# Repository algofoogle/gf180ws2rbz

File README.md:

# gf180ws2rbz: Raybox-zero supporting materials

For now, this is just a test PCB for various parts that could be used to support a raybox-zero devkit.

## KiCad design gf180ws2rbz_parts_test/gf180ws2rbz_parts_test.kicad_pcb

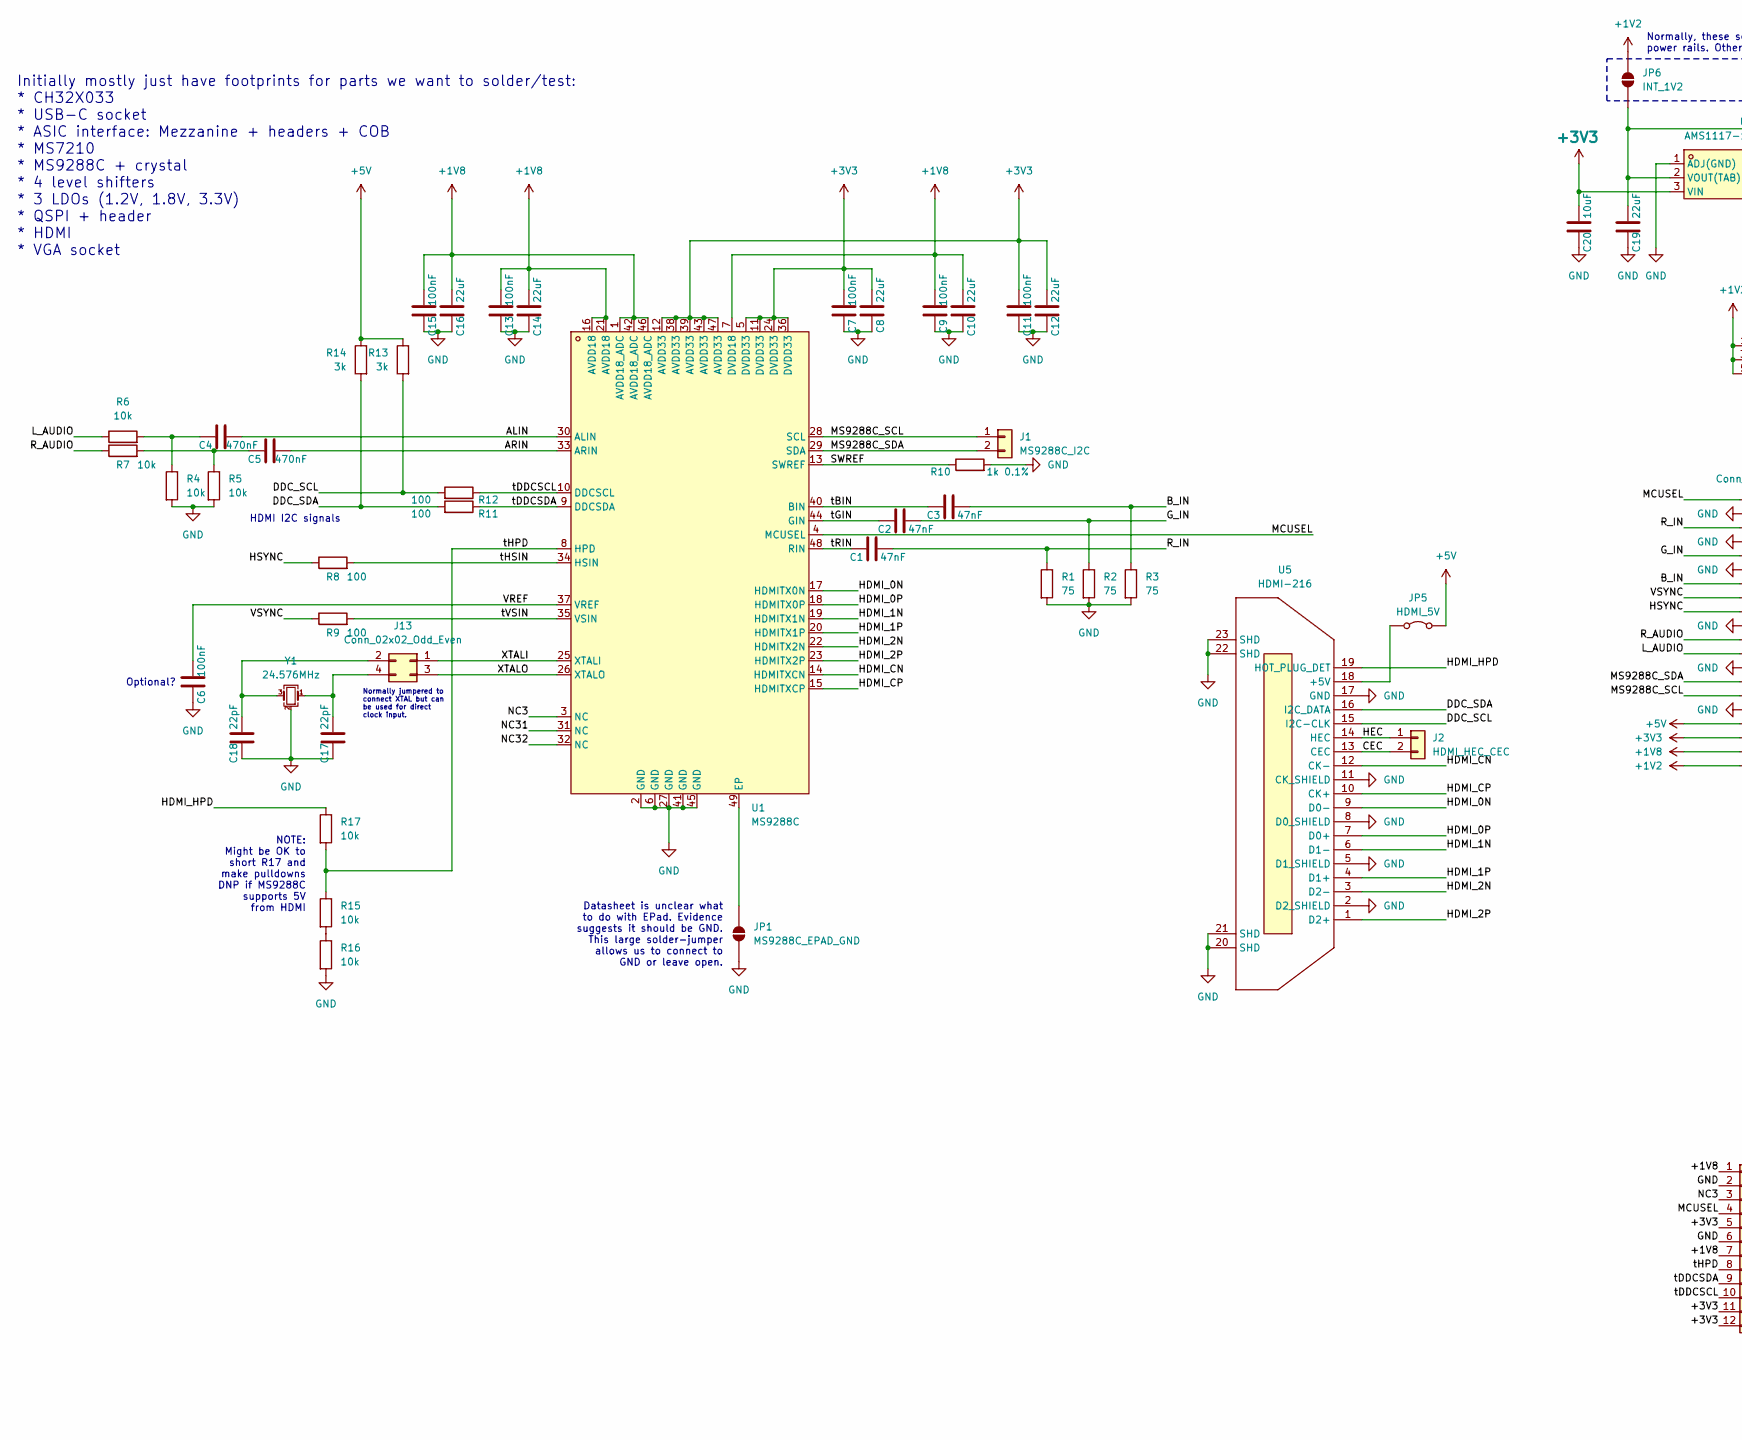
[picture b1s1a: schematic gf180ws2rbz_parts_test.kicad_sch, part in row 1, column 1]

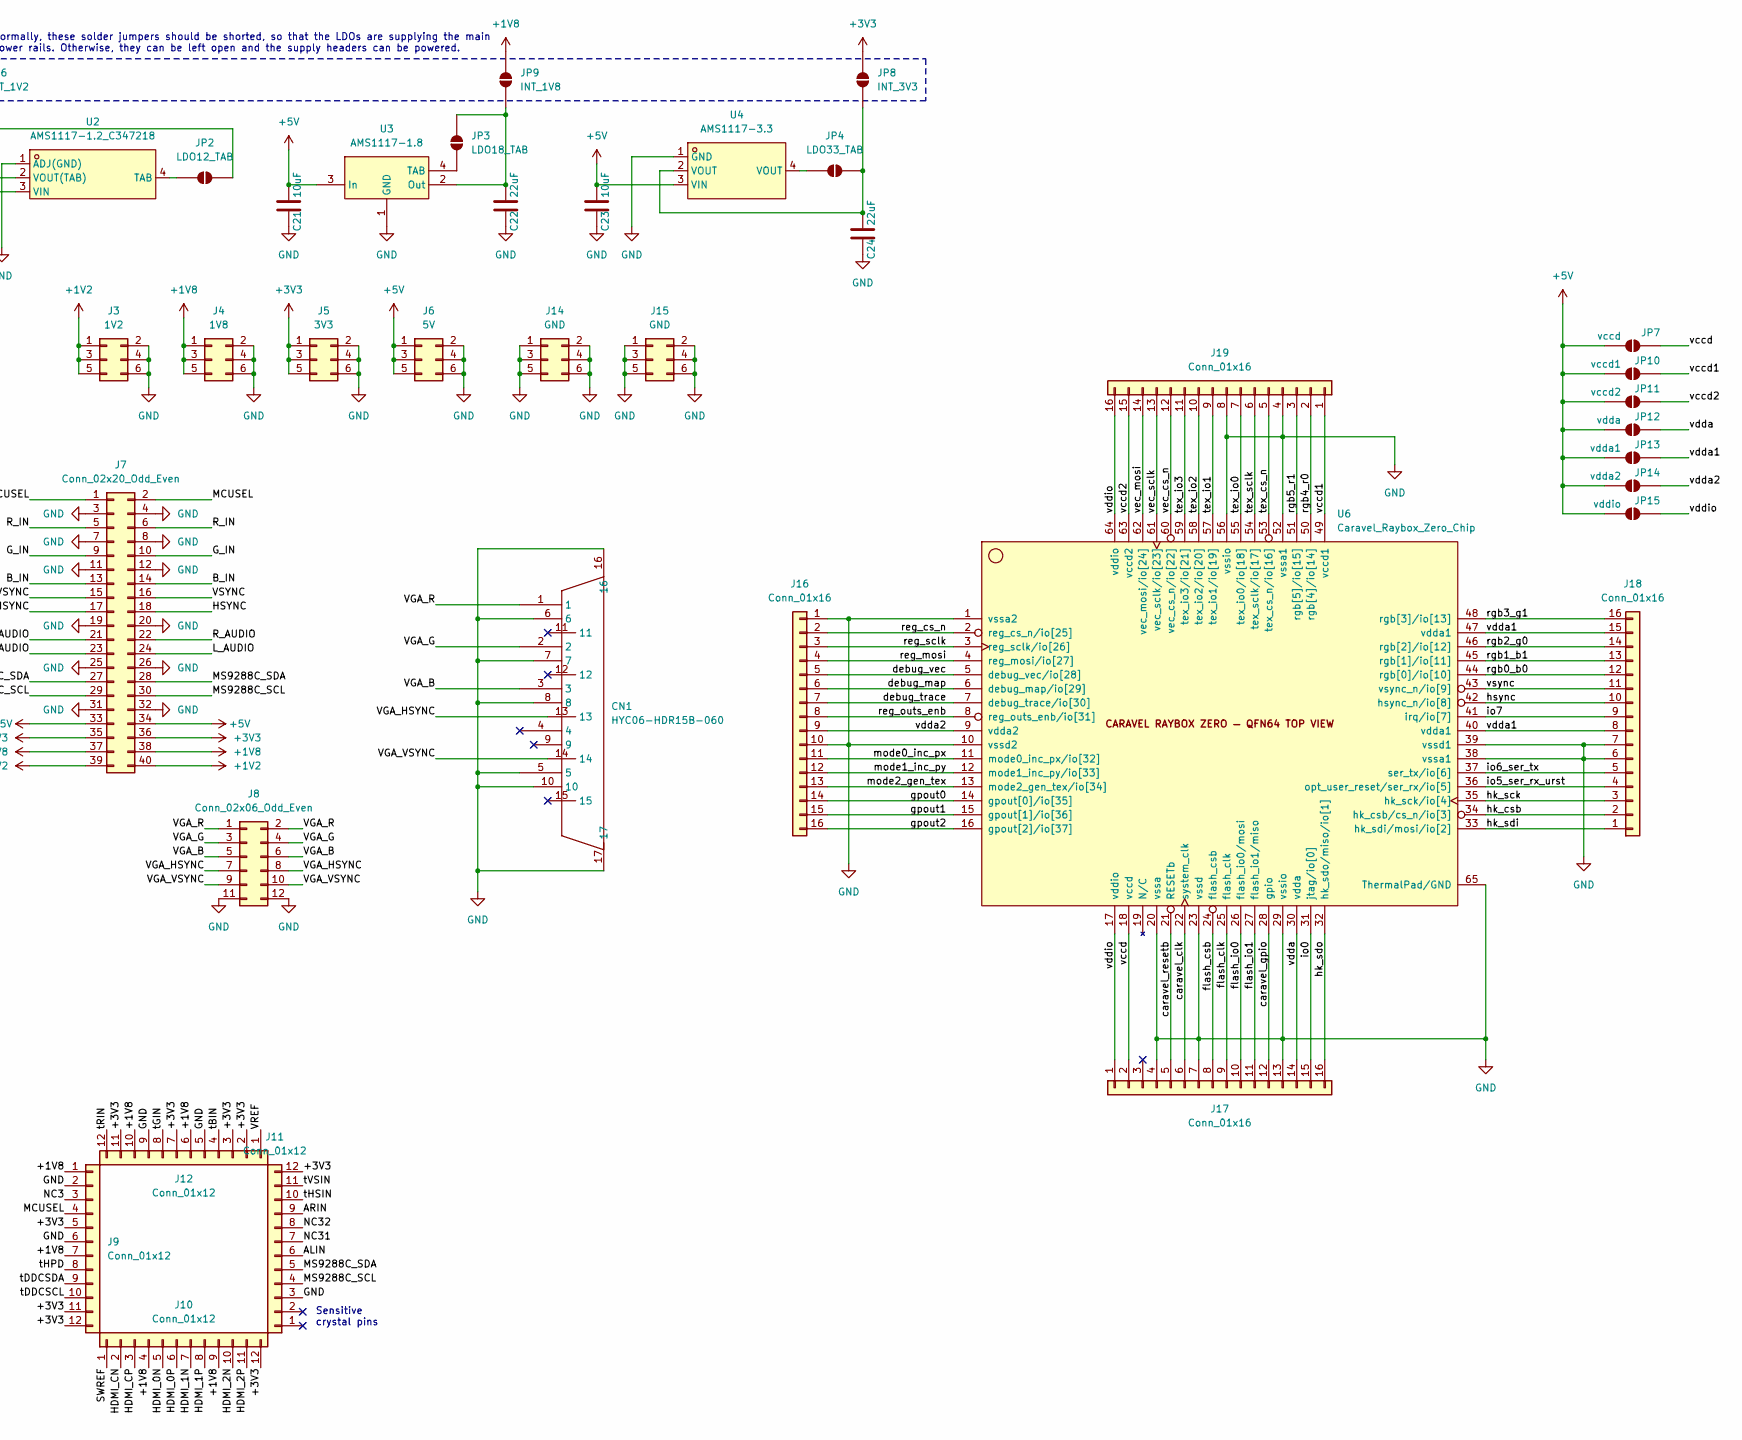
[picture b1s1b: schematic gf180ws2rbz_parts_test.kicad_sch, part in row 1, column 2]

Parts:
C1, C2, C3: 47nF; C_0603_1608Metric_Pad1.08x0.95mm_HandSolder
C4, C5: 470nF; C_0603_1608Metric_Pad1.08x0.95mm_HandSolder
C6, C7, C9, C11, C13, C15: 100nF; C_0603_1608Metric_Pad1.08x0.95mm_HandSolder
C8, C10, C12, C14, C16, C19, C22, C24: 22uF; C_0603_1608Metric_Pad1.08x0.95mm_HandSolder
C17, C18: 22pF; C_0603_1608Metric_Pad1.08x0.95mm_HandSolder
C20, C21, C23: 10uF; C_0603_1608Metric_Pad1.08x0.95mm_HandSolder
CN1: HYC06-HDR15B-060; DSUB-TH_HYC06-HDR15B-060; MPN HYC06-HDR15B-060; LCSC Part C711364
J1: MS9288C_I2C; PinHeader_1x02_P2.54mm_Vertical
J2: HDMI_HEC_CEC; PinHeader_1x02_P2.54mm_Vertical
J3: 1V2; PinHeader_2x03_P2.54mm_Vertical
J4: 1V8; PinHeader_2x03_P2.54mm_Vertical
J5: 3V3; PinHeader_2x03_P2.54mm_Vertical
J6: 5V; PinHeader_2x03_P2.54mm_Vertical
J7: Conn_02x20_Odd_Even; PinHeader_2x20_P2.54mm_Vertical
J8: Conn_02x06_Odd_Even; PinHeader_2x06_P2.54mm_Vertical
J9, J10, J11, J12: Conn_01x12; AntonPTHTestPointStagger12way
J13: Conn_02x02_Odd_Even; Anton-PinSocket_2x02_P2.54mm_Vertical-SolderJumper
J14, J15: GND; PinHeader_2x03_P2.54mm_Vertical
J16, J17, J18, J19: Conn_01x16; Anton_Pads_01x16_1.27mm_Compact_SMD
JP1: MS9288C_EPAD_GND; SolderJumper-2_P1.3mm_Open_RoundedPad1.0x1.5mm
JP2: LDO12_TAB; SolderJumper-2_P1.3mm_Open_RoundedPad1.0x1.5mm
JP3: LDO18_TAB; SolderJumper-2_P1.3mm_Open_RoundedPad1.0x1.5mm
JP4: LDO33_TAB; SolderJumper-2_P1.3mm_Open_RoundedPad1.0x1.5mm
JP5: HDMI_5V; Anton-PinHeader_1x02_P2.54mm_Vertical-SolderJumper
JP6: INT_1V2; SolderJumper-2_P1.3mm_Open_RoundedPad1.0x1.5mm
JP7: vccd; SolderJumper-2_P1.3mm_Open_RoundedPad1.0x1.5mm
JP8: INT_3V3; SolderJumper-2_P1.3mm_Open_RoundedPad1.0x1.5mm
JP9: INT_1V8; SolderJumper-2_P1.3mm_Open_RoundedPad1.0x1.5mm
JP10: vccd1; SolderJumper-2_P1.3mm_Open_RoundedPad1.0x1.5mm
JP11: vccd2; SolderJumper-2_P1.3mm_Open_RoundedPad1.0x1.5mm
JP12: vdda; SolderJumper-2_P1.3mm_Open_RoundedPad1.0x1.5mm
JP13: vdda1; SolderJumper-2_P1.3mm_Open_RoundedPad1.0x1.5mm
JP14: vdda2; SolderJumper-2_P1.3mm_Open_RoundedPad1.0x1.5mm
JP15: vddio; SolderJumper-2_P1.3mm_Open_RoundedPad1.0x1.5mm
R1, R2, R3: 75; R_0603_1608Metric_Pad0.98x0.95mm_HandSolder
R4, R5, R6, R7, R15, R16, R17: 10k; R_0603_1608Metric_Pad0.98x0.95mm_HandSolder
R8, R9, R11, R12: 100; R_0603_1608Metric_Pad0.98x0.95mm_HandSolder
R10: 1k 0.1%; R_0603_1608Metric_Pad0.98x0.95mm_HandSolder
R13, R14: 3k; R_0603_1608Metric_Pad0.98x0.95mm_HandSolder
U1: MS9288C; Anton-QFN-48_L6-W6-P0.4-TL-EP4.2-HandSolder; MPN MS9288C; LCSC Part C2914316
U2: AMS1117-1.2_C347218; SOT-223_L6.7-W3.5-P2.30-BR; MPN AMS1117-1.2; LCSC Part C347218
U3: AMS1117-1.8; SOT-223-4_L6.5-W3.5-P2.30-LS7.0-BR; MPN AMS1117-1.8; LCSC Part C6185
U4: AMS1117-3.3; SOT-223-3_L6.5-W3.4-P2.30-LS7.0-BR; MPN AMS1117-3.3; LCSC Part C6186
U5: HDMI-216; HDMI-SMD_KH-HDMI-19P-CU; MPN HDMI-216; LCSC Part C2962407
U6: Caravel_Raybox_Zero_Chip; Anton-QFN-64-1EP_9x9mm_P0.5mm_EP7.65x7.65mm-HOLE
Y1: 24.576MHz; Crystal_SMD_EuroQuartz_MT-4Pin_3.2x2.5mm_HandSoldering; PartNum XTM32024576JT00351001; LCSC_PartNum C41383247

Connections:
+1V2: J3.1, J3.3, J3.5, J7.39, J7.40, JP6.1 (A)
+1V8: C9.2, C10.2, C13.2, C14.2, C15.2, C16.2, J4.1, J4.3, J4.5, J7.37, J7.38, J9.1, J9.7, J10.4, J10.9, J12.6, J12.10, JP9.1 (A), U1.1 (AVDD18_ADC), U1.7 (DVDD18), U1.16 (AVDD18), U1.21 (AVDD18), U1.42 (AVDD18_ADC), U1.46 (AVDD18_ADC)
+3V3: C7.2, C8.2, C11.2, C12.2, C20.2, J5.1, J5.3, J5.5, J7.35, J7.36, J9.5, J9.11, J9.12, J10.12, J11.12, J12.2, J12.3, J12.7, J12.11, JP8.1 (A), U1.5 (DVDD33), U1.11 (DVDD33), U1.12 (AVDD33), U1.24 (DVDD33), U1.36 (DVDD33), U1.38 (AVDD33), U1.39 (AVDD33), U1.43 (AVDD33), U1.47 (AVDD33), U2.3 (VIN)
/ALIN: C4.2, J11.6, U1.30 (ALIN)
/ARIN: C5.2, J11.9, U1.33 (ARIN)
/CEC: J2.2, U5.13 (CEC)
/DDC_SCL: R12.2, R13.2, U5.15 (I2C-CLK)
/DDC_SDA: R11.2, R14.2, U5.16 (I2C_DATA)
/HDMI_0N: J10.5, U1.17 (HDMITX0N), U5.9 (D0-)
/HDMI_0P: J10.6, U1.18 (HDMITX0P), U5.7 (D0+)
/HDMI_1N: J10.7, U1.19 (HDMITX1N), U5.6 (D1-)
/HDMI_1P: J10.8, U1.20 (HDMITX1P), U5.4 (D1+)
/HDMI_2N: J10.10, U1.22 (HDMITX2N), U5.3 (D2-)
/HDMI_2P: J10.11, U1.23 (HDMITX2P), U5.1 (D2+)
/HDMI_CN: J10.2, U1.14 (HDMITXCN), U5.12 (CK-)
/HDMI_CP: J10.3, U1.15 (HDMITXCP), U5.10 (CK+)
/HDMI_HPD: R17.1, U5.19 (HOT_PLUG_DET)
/HEC: J2.1, U5.14 (HEC)
/HSYNC: J7.17, J7.18, R8.1; also elsewhere on the board
/L_AUDIO: J7.23, J7.24, R6.1
/MCUSEL: J7.1, J7.2, J9.4, U1.4 (MCUSEL)
/MS9288C_SCL: J1.1, J7.29, J7.30, J11.4, U1.28 (SCL)
/MS9288C_SDA: J1.2, J7.27, J7.28, J11.5, U1.29 (SDA)
/NC3: J9.3, U1.3 (NC)
/NC31: J11.7, U1.31 (NC)
/NC32: J11.8, U1.32 (NC)
/R_AUDIO: J7.21, J7.22, R7.1
/SWREF: J10.1, R10.1, U1.13 (SWREF)
/VGA_HSYNC: CN1.13, J8.7, J8.8; also elsewhere on the board
/VGA_VSYNC: CN1.14, J8.9, J8.10; also elsewhere on the board
/VREF: C6.2, J12.1, U1.37 (VREF)
/VSYNC: J7.15, J7.16, R9.1; also elsewhere on the board
/XTALI: J13.1, U1.25 (XTALI)
/XTALO: J13.3, U1.26 (XTALO)
/caravel_clk: J17.6, U6.22 (system_clk)
/caravel_gpio: J17.12, U6.28 (gpio)
/caravel_resetb: J17.5, U6.21 (RESETb)
/debug_map: J16.6, U6.6 (debug_map/io[29])
/debug_trace: J16.7, U6.7 (debug_trace/io[30])
/debug_vec: J16.5, U6.5 (debug_vec/io[28])
/flash_clk: J17.9, U6.25 (flash_clk)
/flash_csb: J17.8, U6.24 (flash_csb)
/flash_io0: J17.10, U6.26 (flash_io0/mosi)
/flash_io1: J17.11, U6.27 (flash_io1/miso)
/gpout0: J16.14, U6.14 (gpout[0]/io[35])
/gpout1: J16.15, U6.15 (gpout[1]/io[36])
/gpout2: J16.16, U6.16 (gpout[2]/io[37])
/hk_csb: J18.2, U6.34 (hk_csb/cs_n/io[3])
/hk_sck: J18.3, U6.35 (hk_sck/io[4])
/hk_sdi: J18.1, U6.33 (hk_sdi/mosi/io[2])
/hk_sdo: J17.16, U6.32 (hk_sdo/miso/io[1])
/hsync: J18.10, U6.42 (hsync_n/io[8])
/io0: J17.15, U6.31 (jtag/io[0])
/io5_ser_rx_urst: J18.4, U6.36 (opt_user_reset/ser_rx/io[5])
/io6_ser_tx: J18.5, U6.37 (ser_tx/io[6])
/io7: J18.9, U6.41 (irq/io[7])
/mode0_inc_px: J16.11, U6.11 (mode0_inc_px/io[32])
/mode1_inc_py: J16.12, U6.12 (mode1_inc_py/io[33])
/mode2_gen_tex: J16.13, U6.13 (mode2_gen_tex/io[34])
/reg_cs_n: J16.2, U6.2 (reg_cs_n/io[25])
/reg_mosi: J16.4, U6.4 (reg_mosi/io[27])
/reg_outs_enb: J16.8, U6.8 (reg_outs_enb/io[31])
/reg_sclk: J16.3, U6.3 (reg_sclk/io[26])
/rgb0_b0: J18.12, U6.44 (rgb[0]/io[10])
/rgb1_b1: J18.13, U6.45 (rgb[1]/io[11])
/rgb2_g0: J18.14, U6.46 (rgb[2]/io[12])
/rgb3_g1: J18.16, U6.48 (rgb[3]/io[13])
/rgb4_r0: J19.2, U6.50 (rgb[4]/io[14])
/rgb5_r1: J19.3, U6.51 (rgb[5]/io[15])
/tBIN: C3.1, J12.4, U1.40 (BIN)
/tDDCSCL: J9.10, R12.1, U1.10 (DDCSCL)
/tDDCSDA: J9.9, R11.1, U1.9 (DDCSDA)
/tGIN: C2.1, J12.8, U1.44 (GIN)
/tHPD: J9.8, R15.1, R17.2, U1.8 (HPD)
/tHSIN: J11.10, R8.2, U1.34 (HSIN)
/tRIN: C1.1, J12.12, U1.48 (RIN)
/tVSIN: J11.11, R9.2, U1.35 (VSIN)
/tex_cs_n: J19.5, U6.53 (tex_cs_n/io[16])
/tex_io0: J19.7, U6.55 (tex_io0/io[18])
/tex_io1: J19.9, U6.57 (tex_io1/io[19])
/tex_io2: J19.10, U6.58 (tex_io2/io[20])
/tex_io3: J19.11, U6.59 (tex_io3/io[21])
/tex_sclk: J19.6, U6.54 (tex_sclk/io[17])
/vdda: J17.14, JP12.1 (A), U6.30 (vdda)
/vdda1: J18.8, J18.15, JP13.1 (A), U6.40 (vdda1), U6.47 (vdda1)
/vdda2: J16.9, JP14.1 (A), U6.9 (vdda2)
/vddio: J17.1, J19.16, JP15.1 (A), U6.17 (vddio), U6.64 (vddio)
/vec_cs_n: J19.12, U6.60 (vec_cs_n/io[22])
/vec_mosi: J19.14, U6.62 (vec_mosi/io[24])
/vec_sclk: J19.13, U6.61 (vec_sclk/io[23])
/vsync: J18.11, U6.43 (vsync_n/io[9])
GND: C6.1, C7.1, C8.1, C9.1, C10.1, C11.1, C12.1, C13.1, C14.1, C15.1, C16.1, C17.1, C18.1, C19.1, C20.1, C21.1, C22.1, C23.1, C24.1, CN1.5, CN1.6, CN1.7, CN1.8, CN1.10, CN1.16, CN1.17, J3.2, J3.4, J3.6, J4.2, J4.4, J4.6, J5.2, J5.4, J5.6, J6.2, J6.4, J6.6, J7.3, J7.4, J7.7, J7.8, J7.11, J7.12, J7.19, J7.20, J7.25, J7.26, J7.31, J7.32, J8.11, J8.12, J9.2, J9.6, J11.3, J12.5, J12.9, J14.1, J14.2, J14.3, J14.4, J14.5, J14.6, J15.1, J15.2, J15.3, J15.4, J15.5, J15.6, J16.1, J16.10, J17.4, J17.7, J17.13, J18.6, J18.7, J19.4, J19.8, JP1.1 (A), R1.2, R2.2, R3.2, R4.2, R5.2, R10.2, R16.2, U1.2 (GND), U1.6 (GND), U1.27 (GND), U1.41 (GND), U1.45 (GND), U2.1 (ADJ(GND)), U3.1 (GND), U4.1 (GND), U5.2 (D2_SHIELD), U5.5 (D1_SHIELD), U5.8 (D0_SHIELD), U5.11 (CK_SHIELD), U5.17 (GND), U5.20 (SHD), U5.21 (SHD), U5.22 (SHD), U5.23 (SHD), U6.1 (vssa2), U6.10 (vssd2), U6.20 (vssa), U6.23 (vssd), U6.29 (vssio), U6.38 (vssa1), U6.39 (vssd1), U6.52 (vssa1), U6.56 (vssio), U6.65 (ThermalPad/GND), Y1.2 (G), Y1.4 (G)
unnamed: C4.1, R4.1, R6.2
unnamed: C5.1, R5.1, R7.2
unnamed: C18.2, J13.2, Y1.3
unnamed: C17.2, J13.4, Y1.1
unnamed: JP1.2 (B), U1.49 (EP)
unnamed: C19.2, JP2.1 (A), JP6.2 (B), U2.2 (VOUT(TAB))
unnamed: JP2.2 (B), U2.4 (TAB)
unnamed: C22.2, JP3.1 (A), JP9.2 (B), U3.2 (Out)
unnamed: JP3.2 (B), U3.4 (TAB)
unnamed: C24.2, JP4.1 (A), JP8.2 (B), U4.2 (VOUT)
unnamed: JP4.2 (B), U4.4 (VOUT)
unnamed: JP5.1 (A), U5.18 (+5V)
unnamed: R15.2, R16.1

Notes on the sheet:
Normally, these solder jumpers should be shorted, so that the LDOs are supplying the main power rails. Otherwise, they can be left open and the supply headers can be powered.
Normally jumpered to connect XTAL but can be used for direct clock input.
Sensitive crystal pins
Optional?
Datasheet is unclear what to do with EPad. Evidence suggests it should be GND. This large solder-jumper allows us to connect to GND or leave open.
HDMI I2C signals
Initially mostly just have footprints for parts we want to solder/test: * CH32X033 * USB-C socket * ASIC interface: Mezzanine + headers + COB * MS7210 * MS9288C + crystal * 4 level shifters * 3 LDOs (1.2V, 1.8V, 3.3V) * QSPI + header * HDMI * VGA socket
NOTE: Might be OK to short R17 and make pulldowns DNP if MS9288C supports 5V from HDMI

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
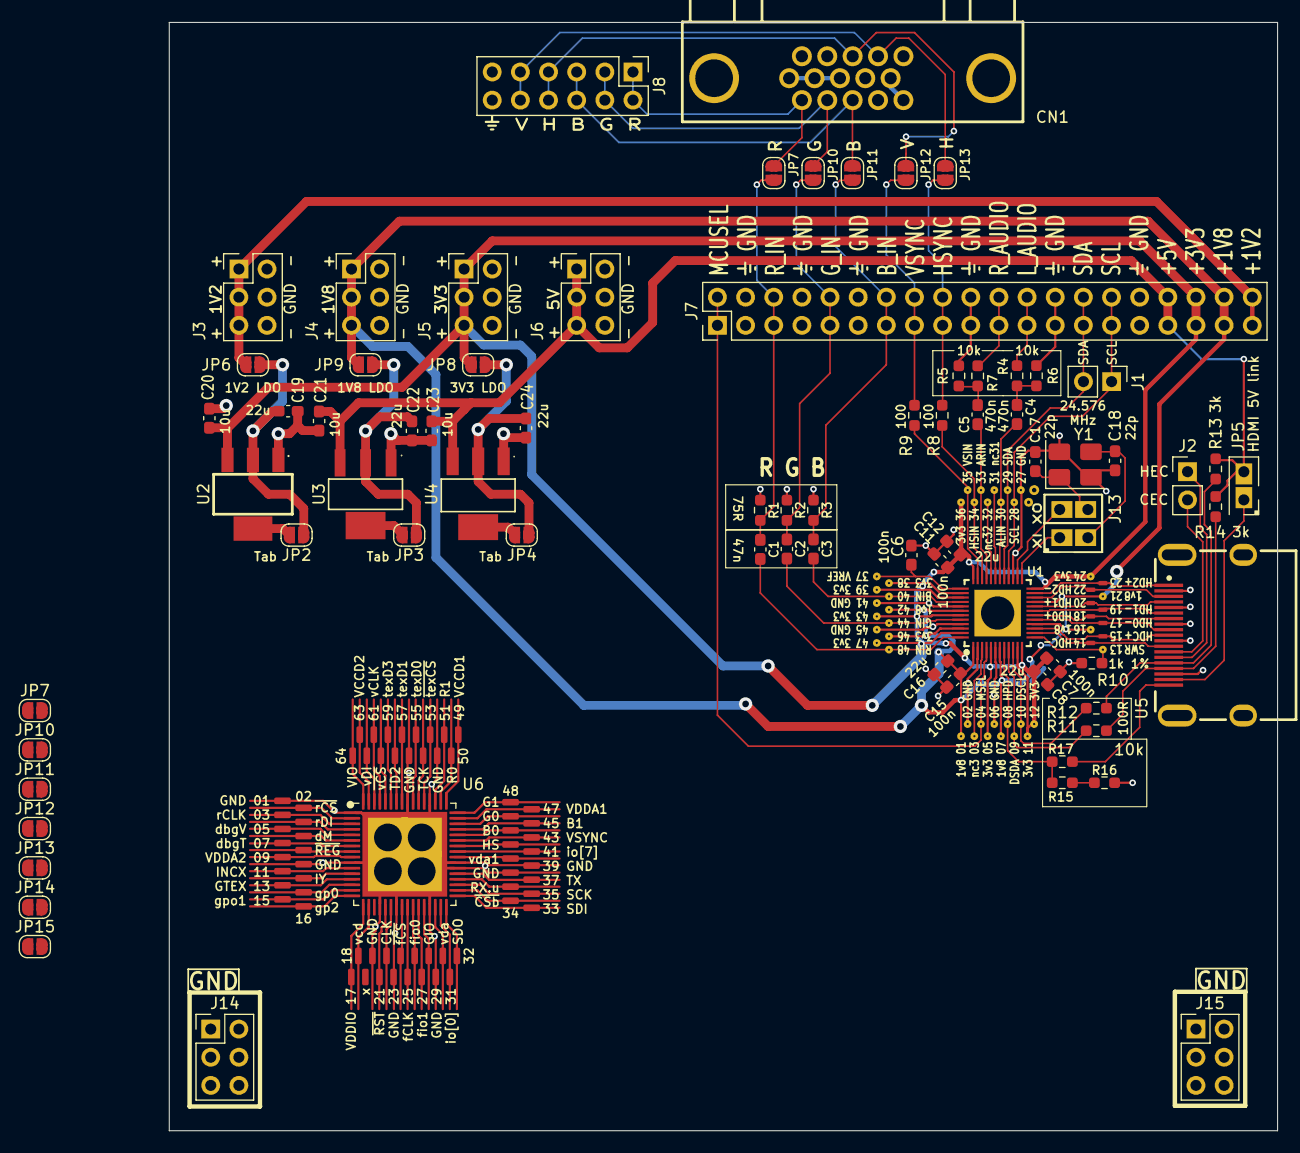
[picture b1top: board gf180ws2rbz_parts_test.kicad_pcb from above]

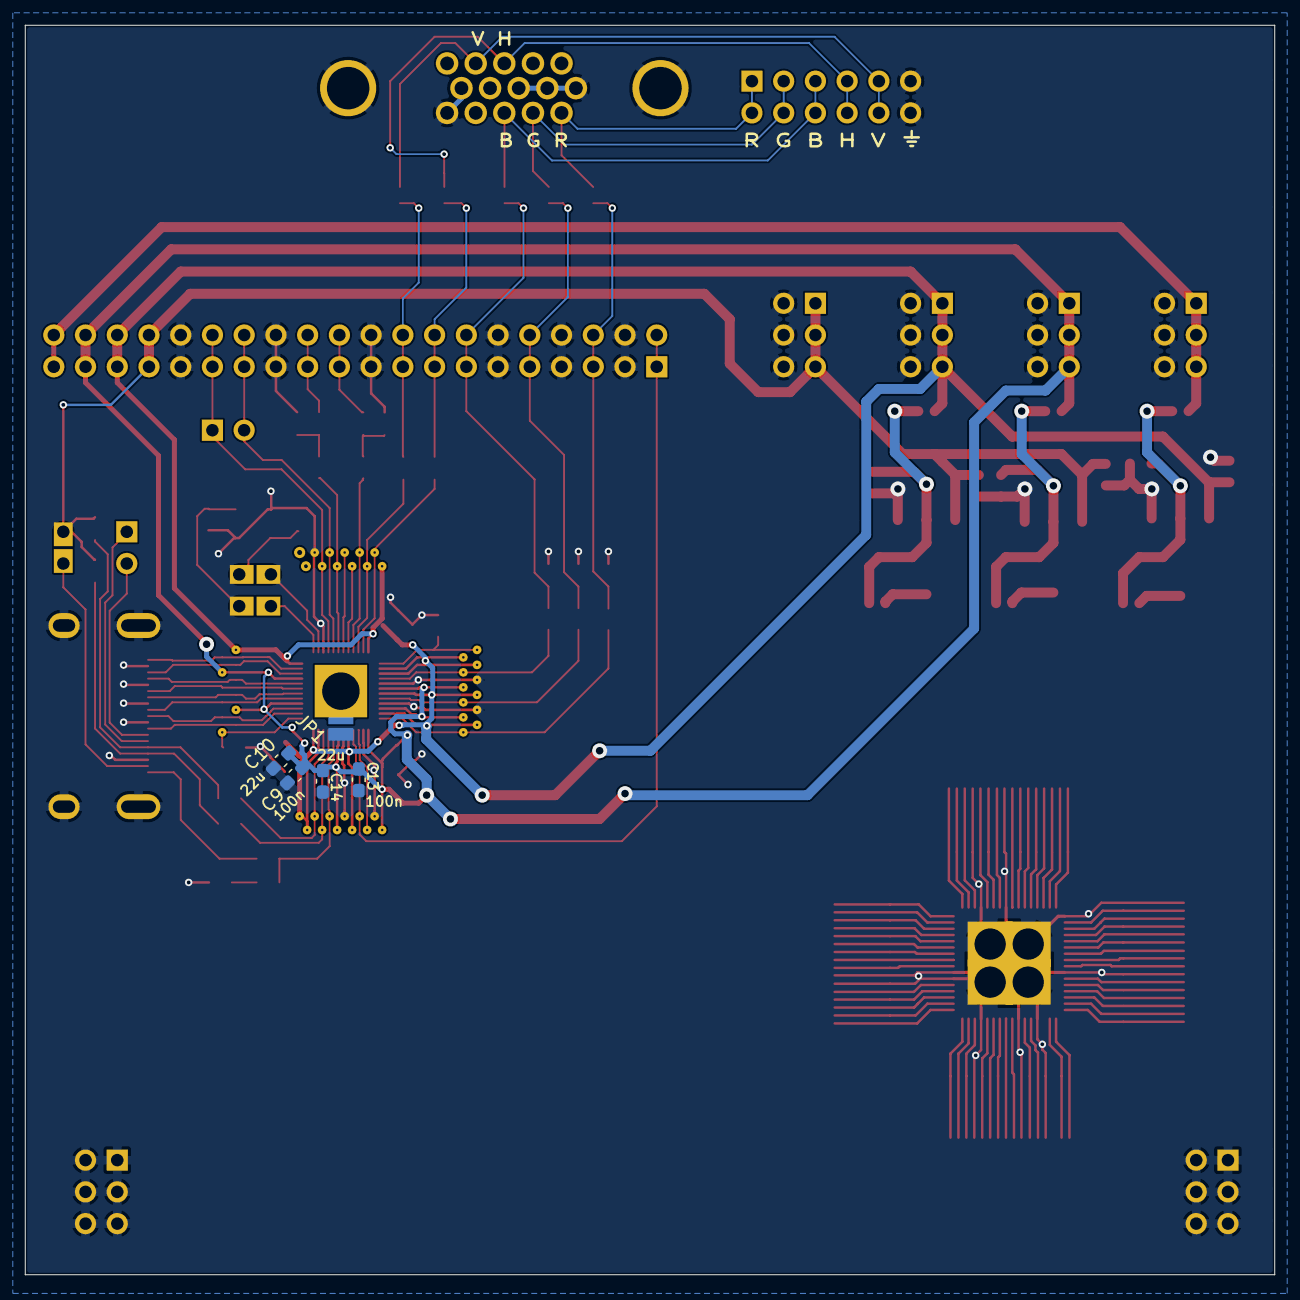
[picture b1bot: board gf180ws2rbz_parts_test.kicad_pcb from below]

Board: 2 copper layers, 100.0 x 100.0 mm, 88 parts (5 on the bottom side), 115 nets.

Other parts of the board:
JP7#2: vccd; SolderJumper-2_P1.3mm_Open_RoundedPad1.0x1.5mm
JP10#2: vccd1; SolderJumper-2_P1.3mm_Open_RoundedPad1.0x1.5mm
JP11#2: vccd2; SolderJumper-2_P1.3mm_Open_RoundedPad1.0x1.5mm
JP12#2, JP13#2: SolderJumper-2_P1.3mm_Open_RoundedPad1.0x1.5mm

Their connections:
/HSYNC: JP13#2.2 (B); also elsewhere on the board
/VGA_HSYNC: JP12#2.1 (A); also elsewhere on the board
/VGA_VSYNC: JP13#2.1 (A); also elsewhere on the board
/VSYNC: JP12#2.2 (B); also elsewhere on the board

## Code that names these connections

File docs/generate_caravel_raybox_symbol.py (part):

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        "RBZ I/O",
        (
            # View-vector SPI slave: io[24:22].
            pin(60, "vec_cs_n/io[22]", "input", "left", shape="inverted"),
            pin(61, "vec_sclk/io[23]", "input", "left", shape="clock"),
            pin(62, "vec_mosi/io[24]", "input", "left"),
            # Register SPI slave: io[27:25].
            pin(2, "reg_cs_n/io[25]", "input", "left", 1, "inverted"),
            pin(3, "reg_sclk/io[26]", "input", "left", shape="clock"),
            pin(4, "reg_mosi/io[27]", "input", "left"),
            # Debug controls: io[30:28].
            pin(5, "debug_vec/io[28]", "input", "left", 1),
            pin(6, "debug_map/io[29]", "input", "left"),
            pin(7, "debug_trace/io[30]", "input", "left"),
            # Active-low registered-output enable: io[31].
            pin(8, "reg_outs_enb/io[31]", "input", "left", 1, "inverted"),
            # Demo mode controls: io[34:32].
            pin(11, "mode0_inc_px/io[32]", "input", "left", 1),
            pin(12, "mode1_inc_py/io[33]", "input", "left"),
            pin(13, "mode2_gen_tex/io[34]", "input", "left"),
            # VGA: io[15:8].
            pin(42, "hsync_n/io[8]", "output", "right", shape="inverted"),
            pin(43, "vsync_n/io[9]", "output", "right", shape="inverted"),
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            pin(51, "rgb[5]/io[15]", "output", "right"),
            # Texture QSPI master: io[21:16].  Keep the bus together even
            # though its individual pins have different directions.
            pin(53, "tex_cs_n/io[16]", "output", "right", 1, "inverted"),
            pin(54, "tex_sclk/io[17]", "output", "right"),
            pin(55, "tex_io0/io[18]", "bidirectional", "right"),
            pin(57, "tex_io1/io[19]", "input", "right"),
            pin(58, "tex_io2/io[20]", "input", "right"),
            pin(59, "tex_io3/io[21]", "input", "right"),
            # General-purpose diagnostic outputs: io[37:35].
            pin(14, "gpout[0]/io[35]", "output", "right", 1),
            pin(15, "gpout[1]/io[36]", "output", "right"),
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        (
            # Housekeeping: io[4:0], kept together on one side.
            pin(31, "jtag/io[0]", "input", "left"),
            pin(32, "hk_sdo/miso/io[1]", "output", "left"),
            pin(33, "hk_sdi/mosi/io[2]", "input", "left"),
            pin(34, "hk_csb/cs_n/io[3]", "input", "left", shape="inverted"),
            pin(35, "hk_sck/io[4]", "input", "left", shape="clock"),
            # Management serial/reset overlays: io[6:5].
            pin(36, "opt_user_reset/ser_rx/io[5]", "input", "left", 1),
            pin(37, "ser_tx/io[6]", "output", "left"),
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            pin(22, "system_clk", "input", "right", shape="clock"),
            # Dedicated management firmware-flash pins 24..27.  In this
            # implementation IO0 is always MOSI/output and IO1 MISO/input.
            pin(24, "flash_csb", "output", "right", 1, "inverted"),
            pin(25, "flash_clk", "output", "right"),
            pin(26, "flash_io0/mosi", "output", "right"),
            pin(27, "flash_io1/miso", "input", "right"),
            # Standalone management GPIO.
            pin(28, "gpio", "bidirectional", "right", 1),
        ),
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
